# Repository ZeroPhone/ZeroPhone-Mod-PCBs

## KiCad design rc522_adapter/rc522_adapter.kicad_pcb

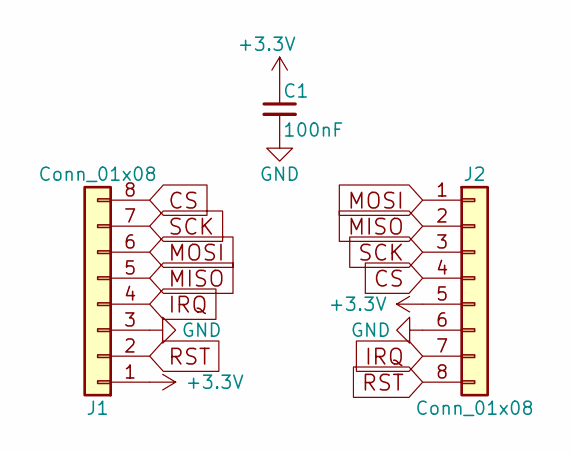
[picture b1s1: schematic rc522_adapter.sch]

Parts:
C1: 100nF; C_0805_HandSoldering
J1, J2: Conn_01x08; Pin_Header_Straight_1x08_Pitch2.54mm

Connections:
+3V3: C1.1, J1.1, J2.5
CS: J1.8, J2.4
GND: C1.2, J1.3, J2.6
IRQ: J1.4, J2.7
MISO: J1.5, J2.2
MOSI: J1.6, J2.1
RST: J1.2, J2.8
SCK: J1.7, J2.3

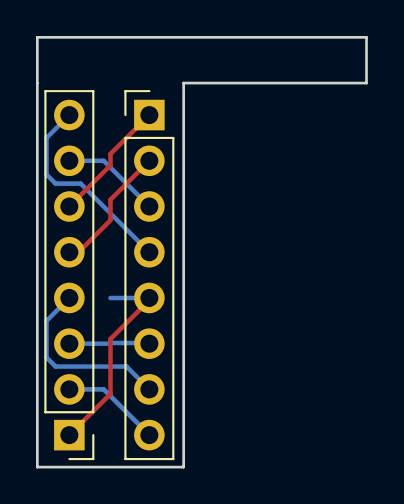
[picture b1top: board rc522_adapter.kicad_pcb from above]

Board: 2 copper layers, 18.3 x 23.9 mm, 3 parts (1 on the bottom side), 8 nets.

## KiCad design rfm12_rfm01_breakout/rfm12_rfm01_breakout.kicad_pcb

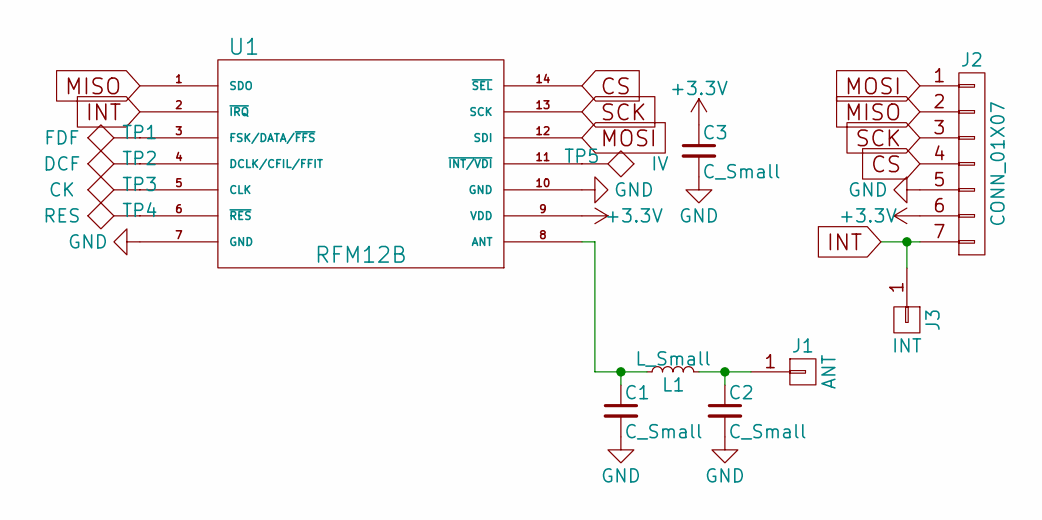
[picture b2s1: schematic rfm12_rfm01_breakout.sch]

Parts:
C1, C2: C_Small; C_0402
C3: C_Small; C_0805_HandSoldering
J1: ANT; Pin_Header_Straight_1x01_Pitch2.54mm
J2: CONN_01X07; Pin_Header_Straight_1x07_Pitch2.54mm
J3: INT; Pin_Header_Straight_1x01_Pitch2.54mm
L1: L_Small; C_0402
TP1: FDF; Measurement_Point_Round-SMD-Pad_Small
TP2: DCF; Measurement_Point_Round-SMD-Pad_Small
TP3: CK; Measurement_Point_Round-SMD-Pad_Small
TP4: RES; Measurement_Point_Round-SMD-Pad_Small
TP5: IV; Measurement_Point_Round-SMD-Pad_Small
U1: RFM12B; flabbergast_rfm12b

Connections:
+3V3: C3.1, J2.6, U1.9 (VDD)
CS: J2.4, U1.14 (~SEL)
GND: C1.2, C2.2, C3.2, J2.5, U1.7 (GND), U1.10 (GND)
INT: J2.7, J3.1, U1.2 (~IRQ)
MISO: J2.2, U1.1 (SDO)
MOSI: J2.1, U1.12 (SDI)
unnamed: C1.1, L1.1, U1.8 (ANT)
unnamed: C2.1, J1.1, L1.2
unnamed: TP1.1, U1.3 (FSK/DATA/~FFS)
unnamed: TP2.1, U1.4 (DCLK/CFIL/FFIT)
unnamed: TP3.1, U1.5 (CLK)
unnamed: TP4.1, U1.6 (~RES)
unnamed: TP5.1, U1.11 (~INT/VDI)
SCK: J2.3, U1.13 (SCK)

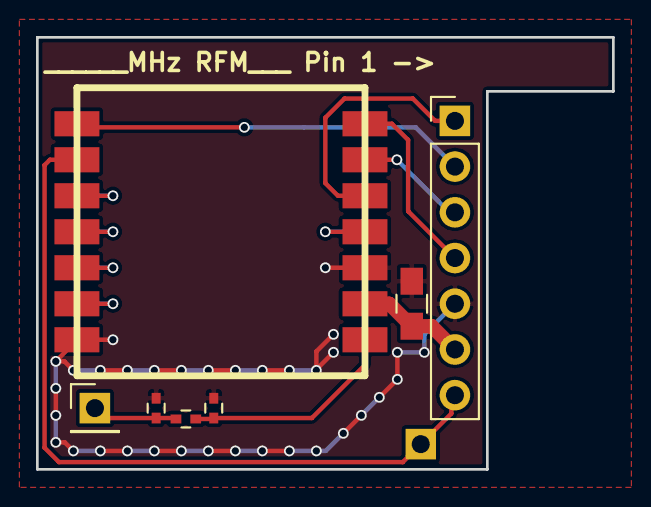
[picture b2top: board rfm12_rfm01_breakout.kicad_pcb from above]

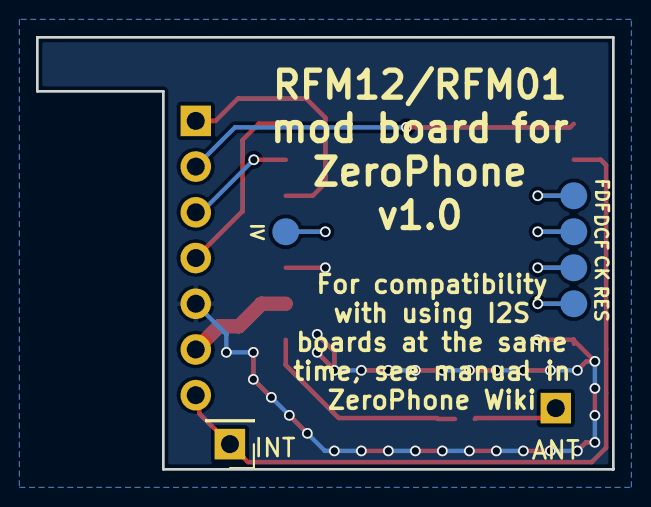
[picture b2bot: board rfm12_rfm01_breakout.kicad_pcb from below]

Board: 2 copper layers, 32.0 x 24.0 mm, 13 parts (6 on the bottom side), 14 nets.

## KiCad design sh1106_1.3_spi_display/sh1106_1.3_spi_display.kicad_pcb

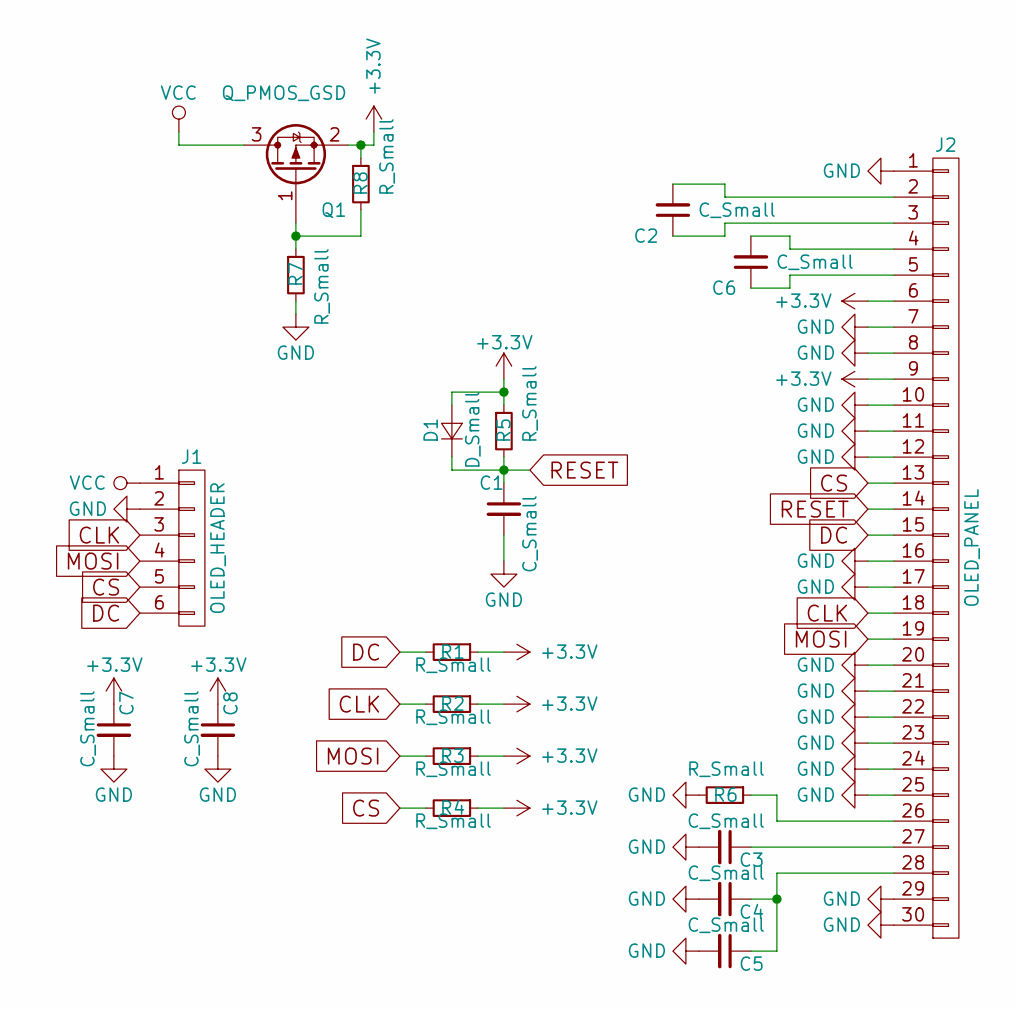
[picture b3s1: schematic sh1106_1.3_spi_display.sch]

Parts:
C1, C2, C3, C4, C5, C6, C7, C8: C_Small; C_0805
D1: D_Small; D_0805
J1: OLED_HEADER; Pin_Header_Straight_1x06_Pitch2.54mm
J2: OLED_PANEL; FPC_30
Q1: Q_PMOS_GSD; SOT-23
R1, R2, R3, R4, R5, R6, R7, R8: R_Small; R_0805

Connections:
+3V3: C7.1, C8.1, D1.2 (A), J2.6, J2.9, Q1.2 (S), R1.1, R2.1, R3.1, R4.1, R5.1, R8.1
CLK: J1.3, J2.18, R2.2
CS: J1.5, J2.13, R4.2
DC: J1.6, J2.15, R1.2
GND: C1.2, C3.2, C4.2, C5.2, C7.2, C8.2, J1.2, J2.1, J2.7, J2.8, J2.10, J2.11, J2.12, J2.16, J2.17, J2.20, J2.21, J2.22, J2.23, J2.24, J2.25, J2.29, J2.30, R6.2, R7.2
MOSI: J1.4, J2.19, R3.2
unnamed: C2.1, J2.3
unnamed: C2.2, J2.2
unnamed: C3.1, J2.27
unnamed: C4.1, C5.1, J2.28
unnamed: C6.1, J2.5
unnamed: C6.2, J2.4
unnamed: J2.26, R6.1
unnamed: Q1.1 (G), R7.1, R8.2
RESET: C1.1, D1.1 (K), J2.14, R5.2
VCC: J1.1, Q1.3 (D)

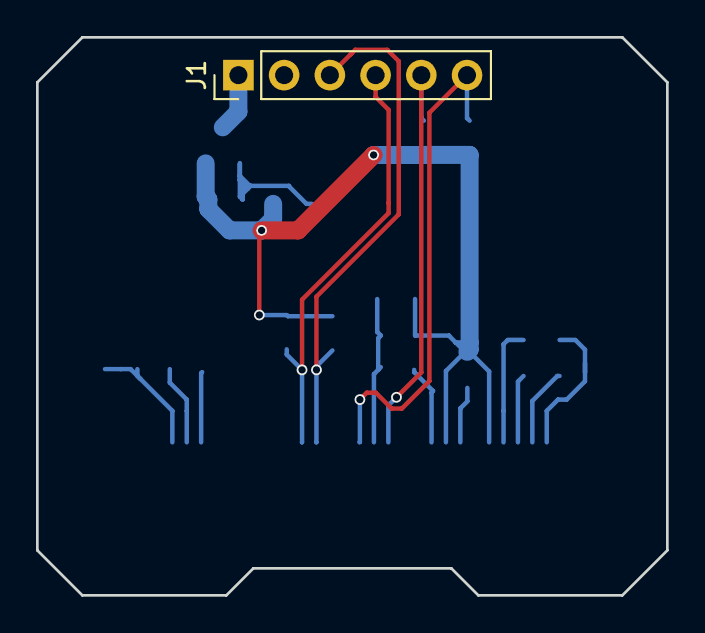
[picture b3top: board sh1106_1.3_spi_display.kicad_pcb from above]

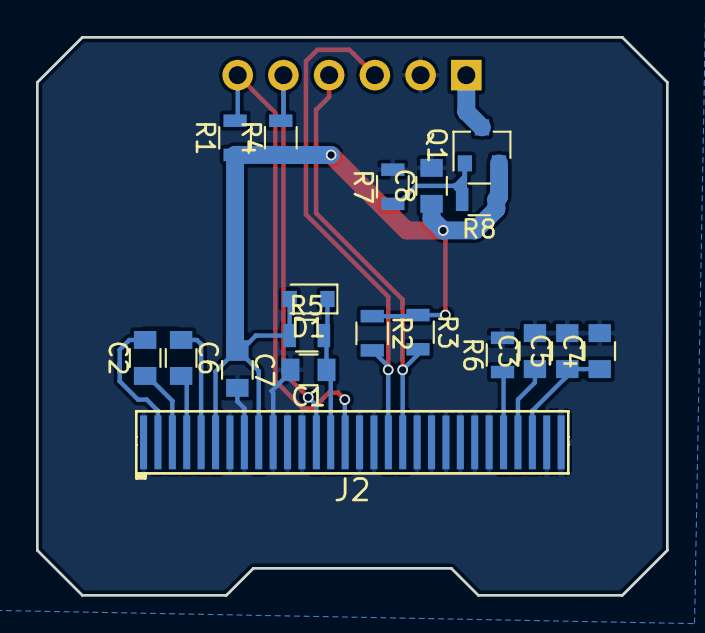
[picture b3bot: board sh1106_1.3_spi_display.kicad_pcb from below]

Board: 2 copper layers, 35.0 x 31.0 mm, 20 parts (19 on the bottom side), 16 nets.

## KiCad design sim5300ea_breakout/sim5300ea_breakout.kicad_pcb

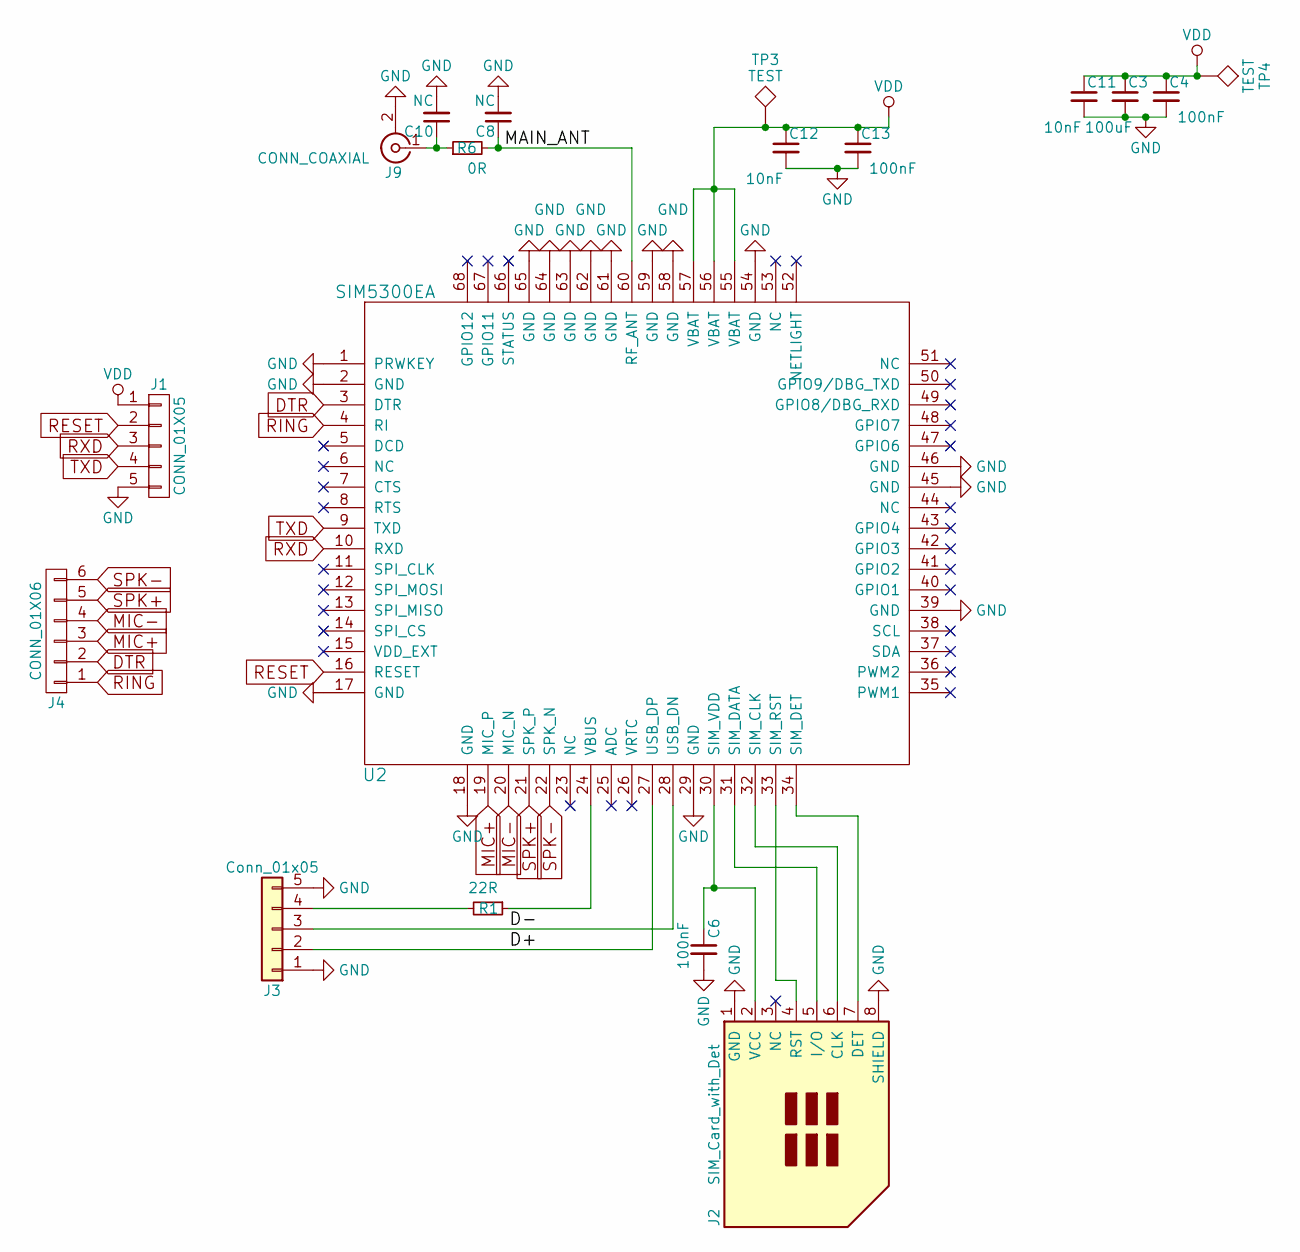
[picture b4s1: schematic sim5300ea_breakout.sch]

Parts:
C3: 100uF; CP_Tantalum_Case-D_EIA-7343-31_Reflow
C4, C6, C13: 100nF; C_0805
C8, C10: NC; C_0402_NoSilk
C11, C12: 10nF; CP_Tantalum_Case-B_EIA-3528-21_Reflow
J1: CONN_01X05; Pin_Header_Straight_1x05_Pitch2.54mm_SMD
J2: SIM_Card_with_Det; MICROSIM_6P_SMD_HOLDER
J3: Conn_01x05; JST_SH_BM04B-SRSS-TB_04x1.00mm_Straight
J4: CONN_01X06; Pin_Header_Straight_1x06_Pitch2.54mm_SMD
J9: CONN_COAXIAL; HRS_U.FL-R-SMT(01)
R1: 22R; R_0603_HandSoldering
R6: 0R; R_0402_NoSilk
TP3, TP4: TEST; Pin_Header_Straight_1x01_Pitch2.54mm
U2: SIM5300EA

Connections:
/D+: J3.2, U2.27 (USB_DP)
/D-: J3.3, U2.28 (USB_DN)
/MAIN_ANT: C8.1, R6.2, U2.60 (RF_ANT)
DTR: J4.2, U2.3 (DTR)
GND: C3.2, C4.2, C6.2, C8.2, C10.2, C11.2, C12.2, C13.2, J1.5, J2.1 (GND), J2.8 (SHIELD), J3.1, J3.5, J9.2 (Ext), U2.1 (PRWKEY), U2.2 (GND), U2.17 (GND), U2.18 (GND), U2.29 (GND), U2.39 (GND), U2.45 (GND), U2.46 (GND), U2.54 (GND), U2.58 (GND), U2.59 (GND), U2.61 (GND), U2.62 (GND), U2.63 (GND), U2.64 (GND), U2.65 (GND)
MIC+: J4.3, U2.19 (MIC_P)
MIC-: J4.4, U2.20 (MIC_N)
unnamed: C6.1, J2.2 (VCC), U2.30 (SIM_VDD)
unnamed: C10.1, J9.1 (In), R6.1
unnamed: J2.4 (RST), U2.33 (SIM_RST)
unnamed: J2.5 (I/O), U2.31 (SIM_DATA)
unnamed: J2.6 (CLK), U2.32 (SIM_CLK)
unnamed: J2.7 (DET), U2.34 (SIM_DET)
unnamed: J3.4, R1.2
unnamed: R1.1, U2.24 (VBUS)
RESET: J1.2, U2.16 (RESET)
RING: J4.1, U2.4 (RI)
RXD: J1.3, U2.10 (RXD)
SPK+: J4.5, U2.21 (SPK_P)
SPK-: J4.6, U2.22 (SPK_N)
TXD: J1.4, U2.9 (TXD)
VDD: C3.1, C4.1, C11.1, C12.1, C13.1, J1.1, TP3.1, TP4.1, U2.55 (VBAT), U2.56 (VBAT), U2.57 (VBAT)

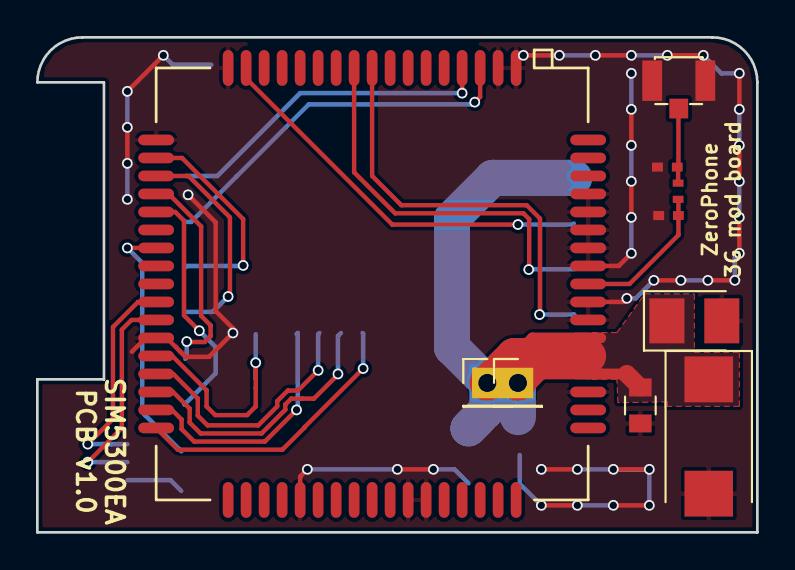
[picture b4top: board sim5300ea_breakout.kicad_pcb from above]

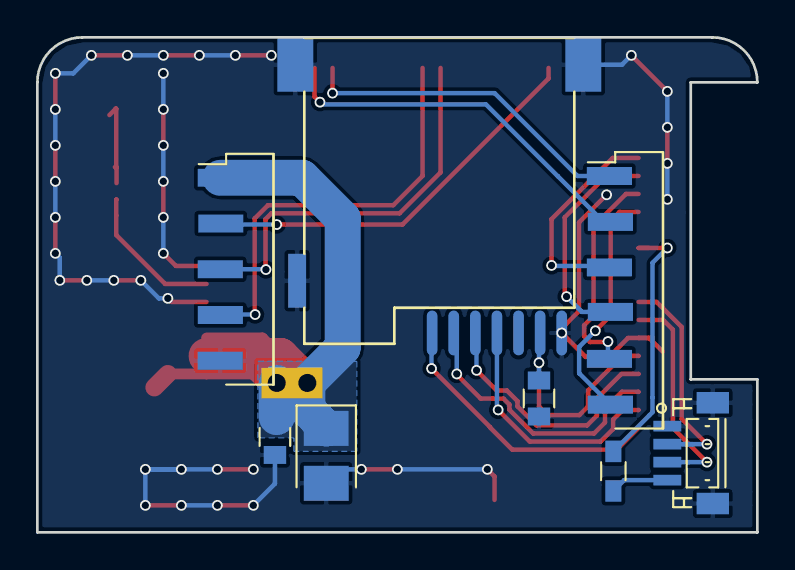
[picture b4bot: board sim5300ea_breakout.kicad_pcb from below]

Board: 2 copper layers, 40.0 x 27.5 mm, 18 parts (8 on the bottom side), 22 nets.

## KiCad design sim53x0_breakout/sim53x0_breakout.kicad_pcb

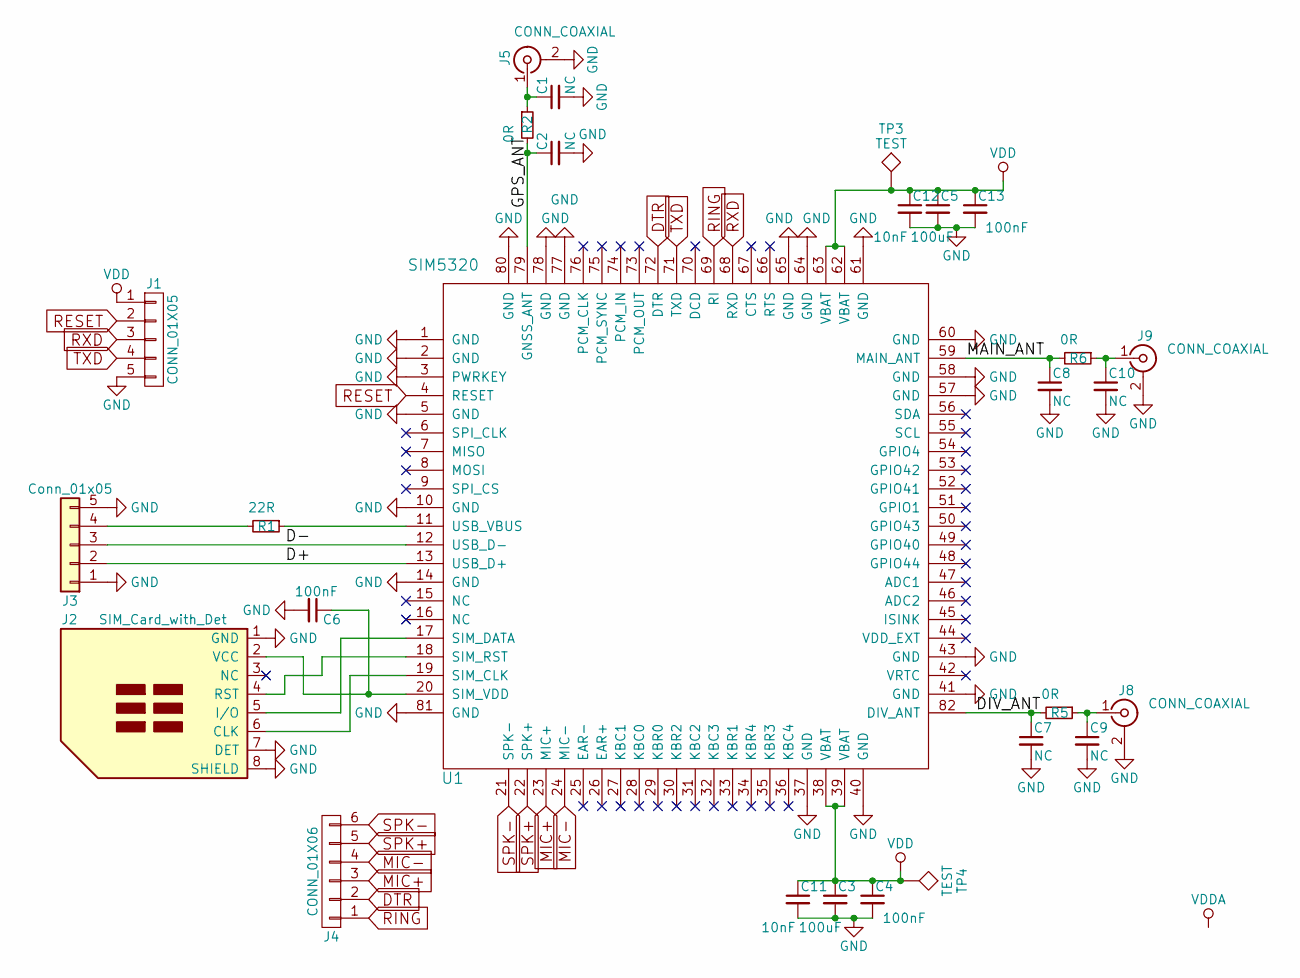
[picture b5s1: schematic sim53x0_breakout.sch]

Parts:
C1, C2, C7, C8, C9, C10: NC; C_0402_NoSilk
C3, C5: 100uF; CP_Tantalum_Case-D_EIA-7343-31_Reflow
C4, C6, C13: 100nF; C_0805
C11, C12: 10nF; CP_Tantalum_Case-B_EIA-3528-21_Reflow
J1: CONN_01X05; Pin_Header_Straight_1x05_Pitch2.54mm_SMD
J2: SIM_Card_with_Det; MICROSIM_6P_SMD_HOLDER
J3: Conn_01x05; JST_SH_BM04B-SRSS-TB_04x1.00mm_Straight
J4: CONN_01X06; Pin_Header_Straight_1x06_Pitch2.54mm_SMD
J5, J8, J9: CONN_COAXIAL; HRS_U.FL-R-SMT(01)
R1: 22R; R_0603_HandSoldering
R2, R5, R6: 0R; R_0402_NoSilk
TP3, TP4: TEST; Pin_Header_Straight_1x01_Pitch2.54mm
U1: SIM5320

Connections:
/D+: J3.2, U1.13 (USB_D+)
/D-: J3.3, U1.12 (USB_D-)
/DIV_ANT: C7.1, R5.2, U1.82 (DIV_ANT)
/GPS_ANT: C2.1, R2.2, U1.79 (GNSS_ANT)
/MAIN_ANT: C8.1, R6.2, U1.59 (MAIN_ANT)
DTR: J4.2, U1.72 (DTR)
GND: C1.2, C2.2, C3.2, C4.2, C5.2, C6.2, C7.2, C8.2, C9.2, C10.2, C11.2, C12.2, C13.2, J1.5, J2.1 (GND), J2.7 (DET), J2.8 (SHIELD), J3.1, J3.5, J5.2 (Ext), J8.2 (Ext), J9.2 (Ext), U1.1 (GND), U1.2 (GND), U1.3 (PWRKEY), U1.5 (GND), U1.10 (GND), U1.14 (GND), U1.37 (GND), U1.40 (GND), U1.41 (GND), U1.43 (GND), U1.57 (GND), U1.58 (GND), U1.60 (GND), U1.61 (GND), U1.64 (GND), U1.65 (GND), U1.77 (GND), U1.78 (GND), U1.80 (GND), U1.81 (GND)
MIC+: J4.3, U1.23 (MIC+)
MIC-: J4.4, U1.24 (MIC-)
unnamed: C1.1, J5.1 (In), R2.1
unnamed: C6.1, J2.2 (VCC), U1.20 (SIM_VDD)
unnamed: C9.1, J8.1 (In), R5.1
unnamed: C10.1, J9.1 (In), R6.1
unnamed: J2.4 (RST), U1.18 (SIM_RST)
unnamed: J2.5 (I/O), U1.17 (SIM_DATA)
unnamed: J2.6 (CLK), U1.19 (SIM_CLK)
unnamed: J3.4, R1.2
unnamed: R1.1, U1.11 (USB_VBUS)
RESET: J1.2, U1.4 (RESET)
RING: J4.1, U1.69 (RI)
RXD: J1.3, U1.68 (RXD)
SPK+: J4.5, U1.22 (SPK+)
SPK-: J4.6, U1.21 (SPK-)
TXD: J1.4, U1.71 (TXD)
VDD: C3.1, C4.1, C5.1, C11.1, C12.1, C13.1, J1.1, TP3.1, TP4.1, U1.38 (VBAT), U1.39 (VBAT), U1.62 (VBAT), U1.63 (VBAT)

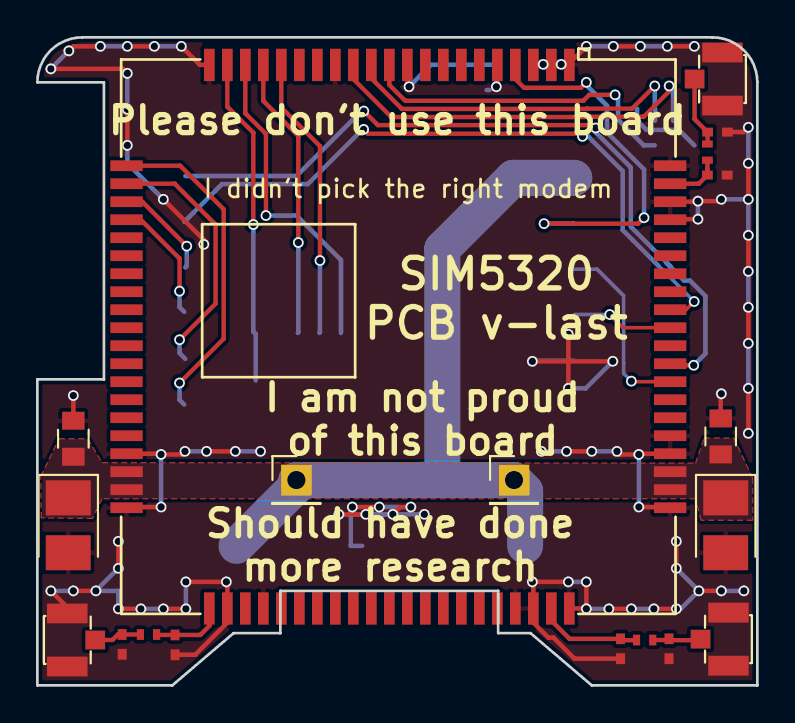
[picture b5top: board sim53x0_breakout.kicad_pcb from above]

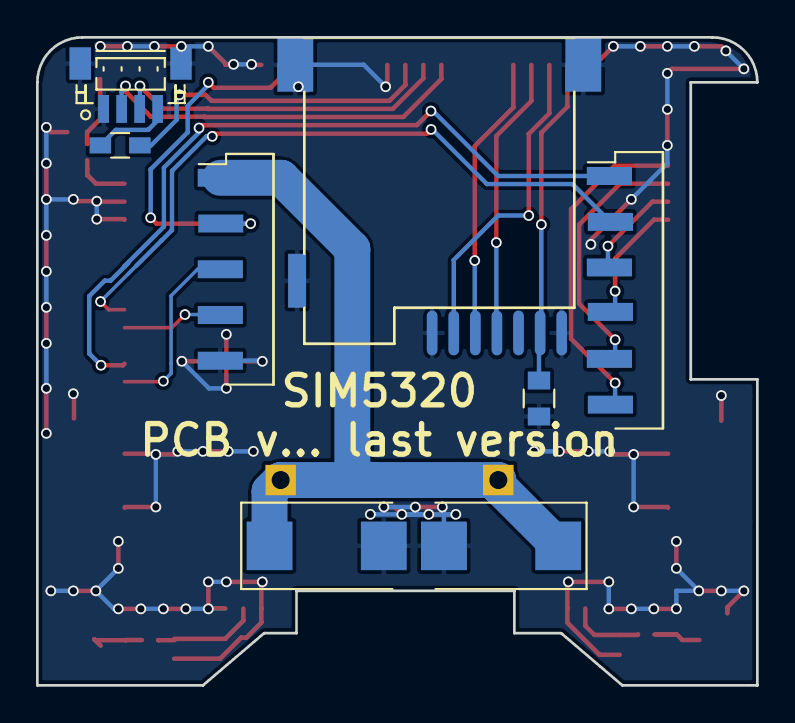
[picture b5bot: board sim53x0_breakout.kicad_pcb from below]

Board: 2 copper layers, 40.0 x 36.0 mm, 27 parts (8 on the bottom side), 25 nets.

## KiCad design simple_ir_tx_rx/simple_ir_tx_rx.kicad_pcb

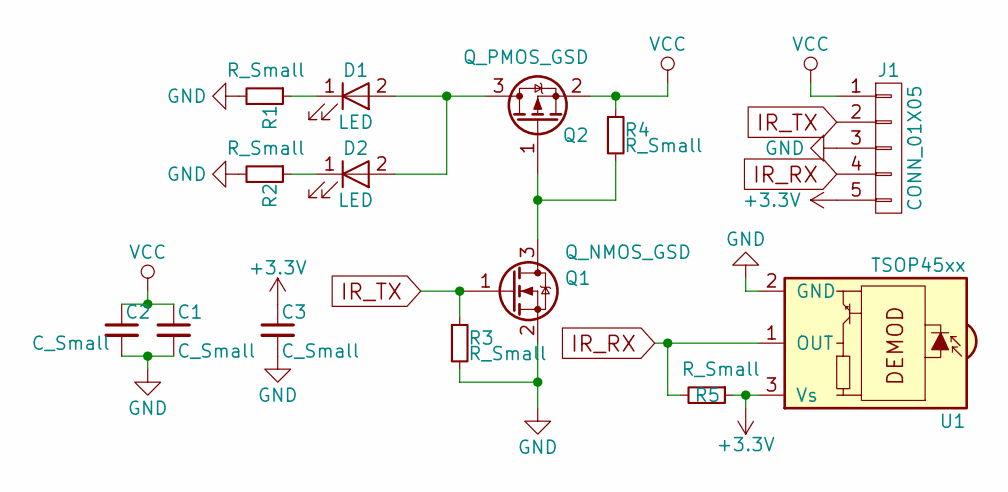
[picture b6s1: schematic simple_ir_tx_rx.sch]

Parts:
C1, C2, C3: C_Small; C_0805
D1, D2: LED; LED_D5.0mm_Horizontal_O1.27mm_Z3.0mm
J1: CONN_01X05; Pin_Header_Angled_1x05_Pitch2.54mm
Q1: Q_NMOS_GSD; SOT-23_Handsoldering
Q2: Q_PMOS_GSD; SOT-23_Handsoldering
R1, R2: R_Small; R_0805
R3, R4, R5: R_Small; R_0603_HandSoldering
U1: TSOP45xx; IRReceiver_Vishay_MOLD-3pin

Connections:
+3V3: C3.1, J1.5, R5.1, U1.3 (Vs)
GND: C1.2, C2.2, C3.2, J1.3, Q1.2 (S), R1.2, R2.2, R3.2, U1.2 (GND)
IR_RX: J1.4, R5.2, U1.1 (OUT)
IR_TX: J1.2, Q1.1 (G), R3.1
unnamed: D1.1 (K), R1.1
unnamed: D1.2 (A), D2.2 (A), Q2.3 (D)
unnamed: D2.1 (K), R2.1
unnamed: Q1.3 (D), Q2.1 (G), R4.2
VCC: C1.1, C2.1, J1.1, Q2.2 (S), R4.1

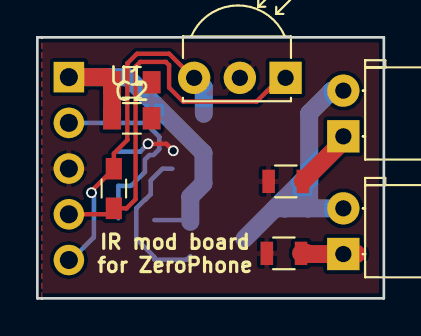
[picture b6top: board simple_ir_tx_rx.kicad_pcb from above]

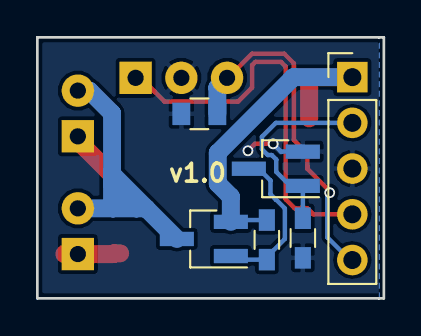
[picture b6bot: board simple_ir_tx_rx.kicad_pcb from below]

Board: 2 copper layers, 19.2 x 14.5 mm, 14 parts (6 on the bottom side), 9 nets.

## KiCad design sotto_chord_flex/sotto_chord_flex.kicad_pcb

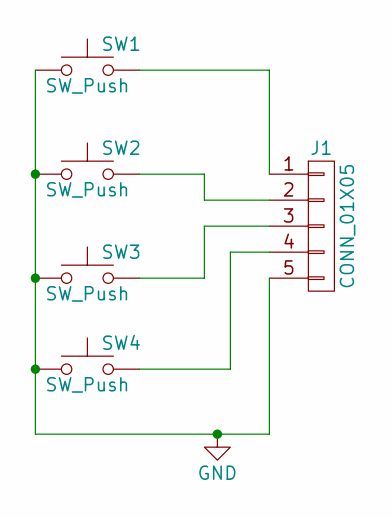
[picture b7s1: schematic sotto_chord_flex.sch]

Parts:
J1: CONN_01X05; Pin_Header_Straight_1x05_Pitch2.00mm
SW1, SW2, SW3, SW4: SW_Push; SW_SPST_B3S-1000

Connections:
GND: J1.5, SW1.1, SW2.1, SW3.1, SW4.1
unnamed: J1.1, SW1.2
unnamed: J1.2, SW2.2
unnamed: J1.3, SW3.2
unnamed: J1.4, SW4.2

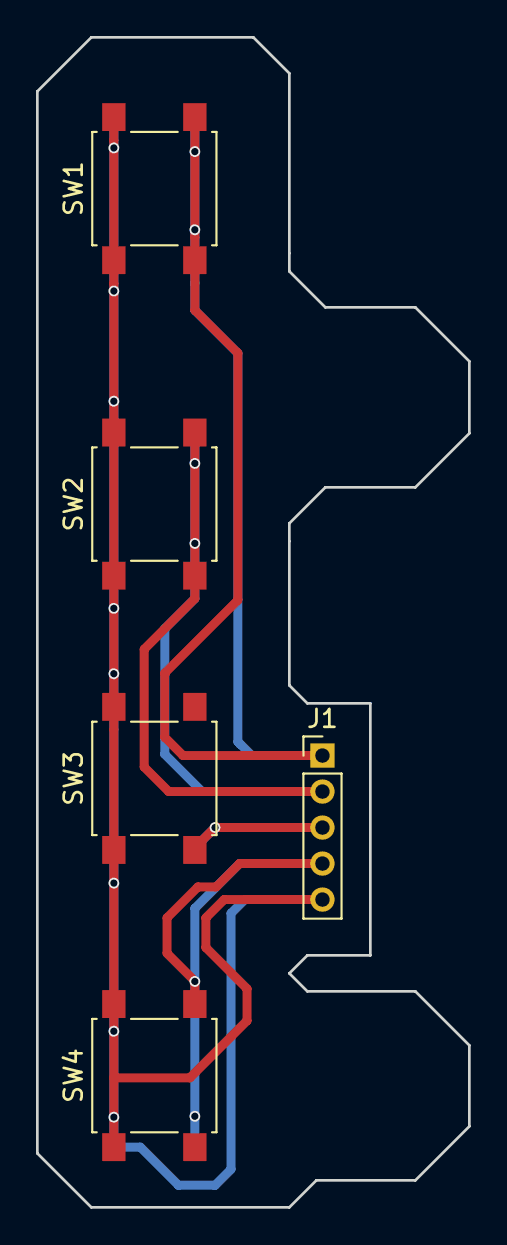
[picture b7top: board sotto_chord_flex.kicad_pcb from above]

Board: 2 copper layers, 24.0 x 65.0 mm, 5 parts (0 on the bottom side), 5 nets.

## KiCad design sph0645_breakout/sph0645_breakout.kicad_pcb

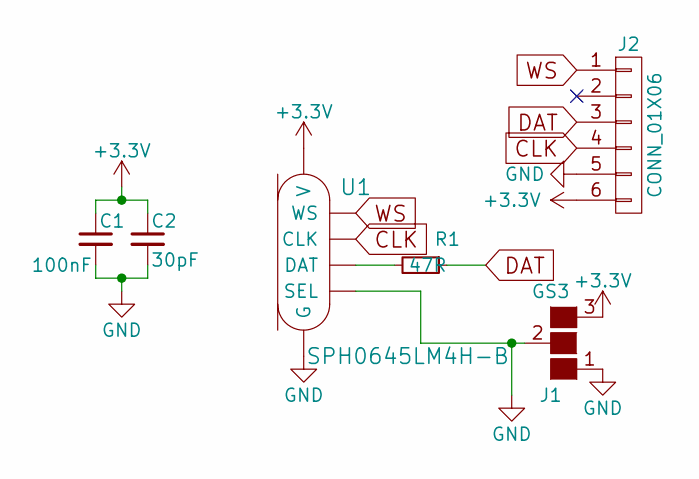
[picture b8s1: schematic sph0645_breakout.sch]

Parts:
C1: 100nF; C_0603
C2: 30pF; C_0603
J1: GS3
J2: CONN_01X06; Pin_Header_Straight_1x06_Pitch2.54mm
R1: 47R; R_0603_HandSoldering
U1: SPH0645LM4H-B; SPH_I2S

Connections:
+3V3: C1.1, C2.1, J1.3 (G3), J2.6, U1.5 (V)
CLK: J2.4, U1.4 (CLK)
DAT: J2.3, R1.1
GND: C1.2, C2.2, J1.1 (G1), J1.2 (G2), J2.5, U1.2 (SEL), U1.3 (G)
unnamed: R1.2, U1.6 (DAT)
WS: J2.1, U1.1 (WS)
